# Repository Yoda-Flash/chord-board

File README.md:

# Chord Board
The Chord Board is a MIDI controller, specifically designed for one to experiment with chords! 
Each note you play can be customized and looped.

I came up with this idea because I've always loved playing with different chords. 
I thought it would be cool to be able to experiment with them without having an actual instrument with me, 
or needing to learn the chords and fingerings to hear different combinations.

## Images
### CAD
Top view:

Bottom view:

CAD of PCB with parts:

### PCB
PCB:

3D PCB Front:

3D PCB Back:

## Features
### Keypad
- 9 keys in a matrix
- 7 keys to activate chords
  - E.g. Pressing "I" will play the root chord, and "V" will play the fifth
- 2 keys to raise or lower the current key (default is C4)

### Rotary Potentiometers
- 7 knobs to modify chords
  - One knob for each note in the chord (1, 3, 5, 7, 9, 11, 13)
  - Each knob has 5 markings: ♭♭, ♭, no modification, #, ## (from left to right)
  - Modifications get applied to the next chord activated
  - If you don't want to include the note in the chord, just rotate the knob to any other position
  - E.g. If the 1st knob is not modified, the 2nd knob is at ♭, and the 3rd knob is not modified, a minor triad will play
- 1 logarithmic knob to adjust volume

### Slide potentiometer
- Inverts the chord depending on how much you slide
  - E.g. If a minor triad is playing and you slide 1/3 of the way, the base note will become the 5th

### Latching buttons
- 1 to cycle through different octaves, between octaves 2 to 6
- 1 to record a loop
  - When pressed, the chord sequence and timing will be recorded
  - When released, the chord sequence will be played back until you re-record or press another key

### TFT Display
- Displays the current key, including the octave, and the notes of the chord being played
  - If the notes being played are matched with a chord, that chord's name will be displayed as well

### Speakers
- Stereo sound
- Left and right speakers connected to a Class D Amplifier

### Power system
- 18650 3.7 V battery 
  - When a USB is plugged into the microcontroller, it will automatically charge
- Switch to power the board on/off
- A cover secures the battery, to be screwed open
  - Comes with a groove for fingers to easily remove the cover

### Stackable Case Cover
- The case comes with a cover, so the device can be transported without fear of accidentally pressing keys or rotating knobs
- The cover can be stacked on the bottom cover, so it doesn't have to lie around when the device is in use

## Bill of Materials
[CSV](bom.csv)

[Excel XLSX](bom.xlsx)

## How to Set Up

### Build Instructions
Gather the assembled PCB and the 3D printed pieces in the [cad folder](./cad), as well as 4 sets of M3 12mm screws and heat inserts and 1 set of M2 3mm screws and heat inserts. 

Use a soldering iron to set the heat inserts in their respective holes (M2 3mm into the bottom case's back holes for the battery cover and M3 12mm for the bottom case's top holes for PCB mounting). Then, place the PCB in between the top and bottom case, and a battery and its cover into the slot on the back. Use a 2mm hex key to screw in the M2 screws and a 3mm hex key for the M3 one.

### Firmware Instructions
The firmware uses Circuit Python, 
so get started with it following https://learn.adafruit.com/welcome-to-circuitpython/installing-circuitpython

Within the Circuit Python drive, 
use pip to install the requirements in `requirements.txt` and transfer the files from `./firmware` to use!

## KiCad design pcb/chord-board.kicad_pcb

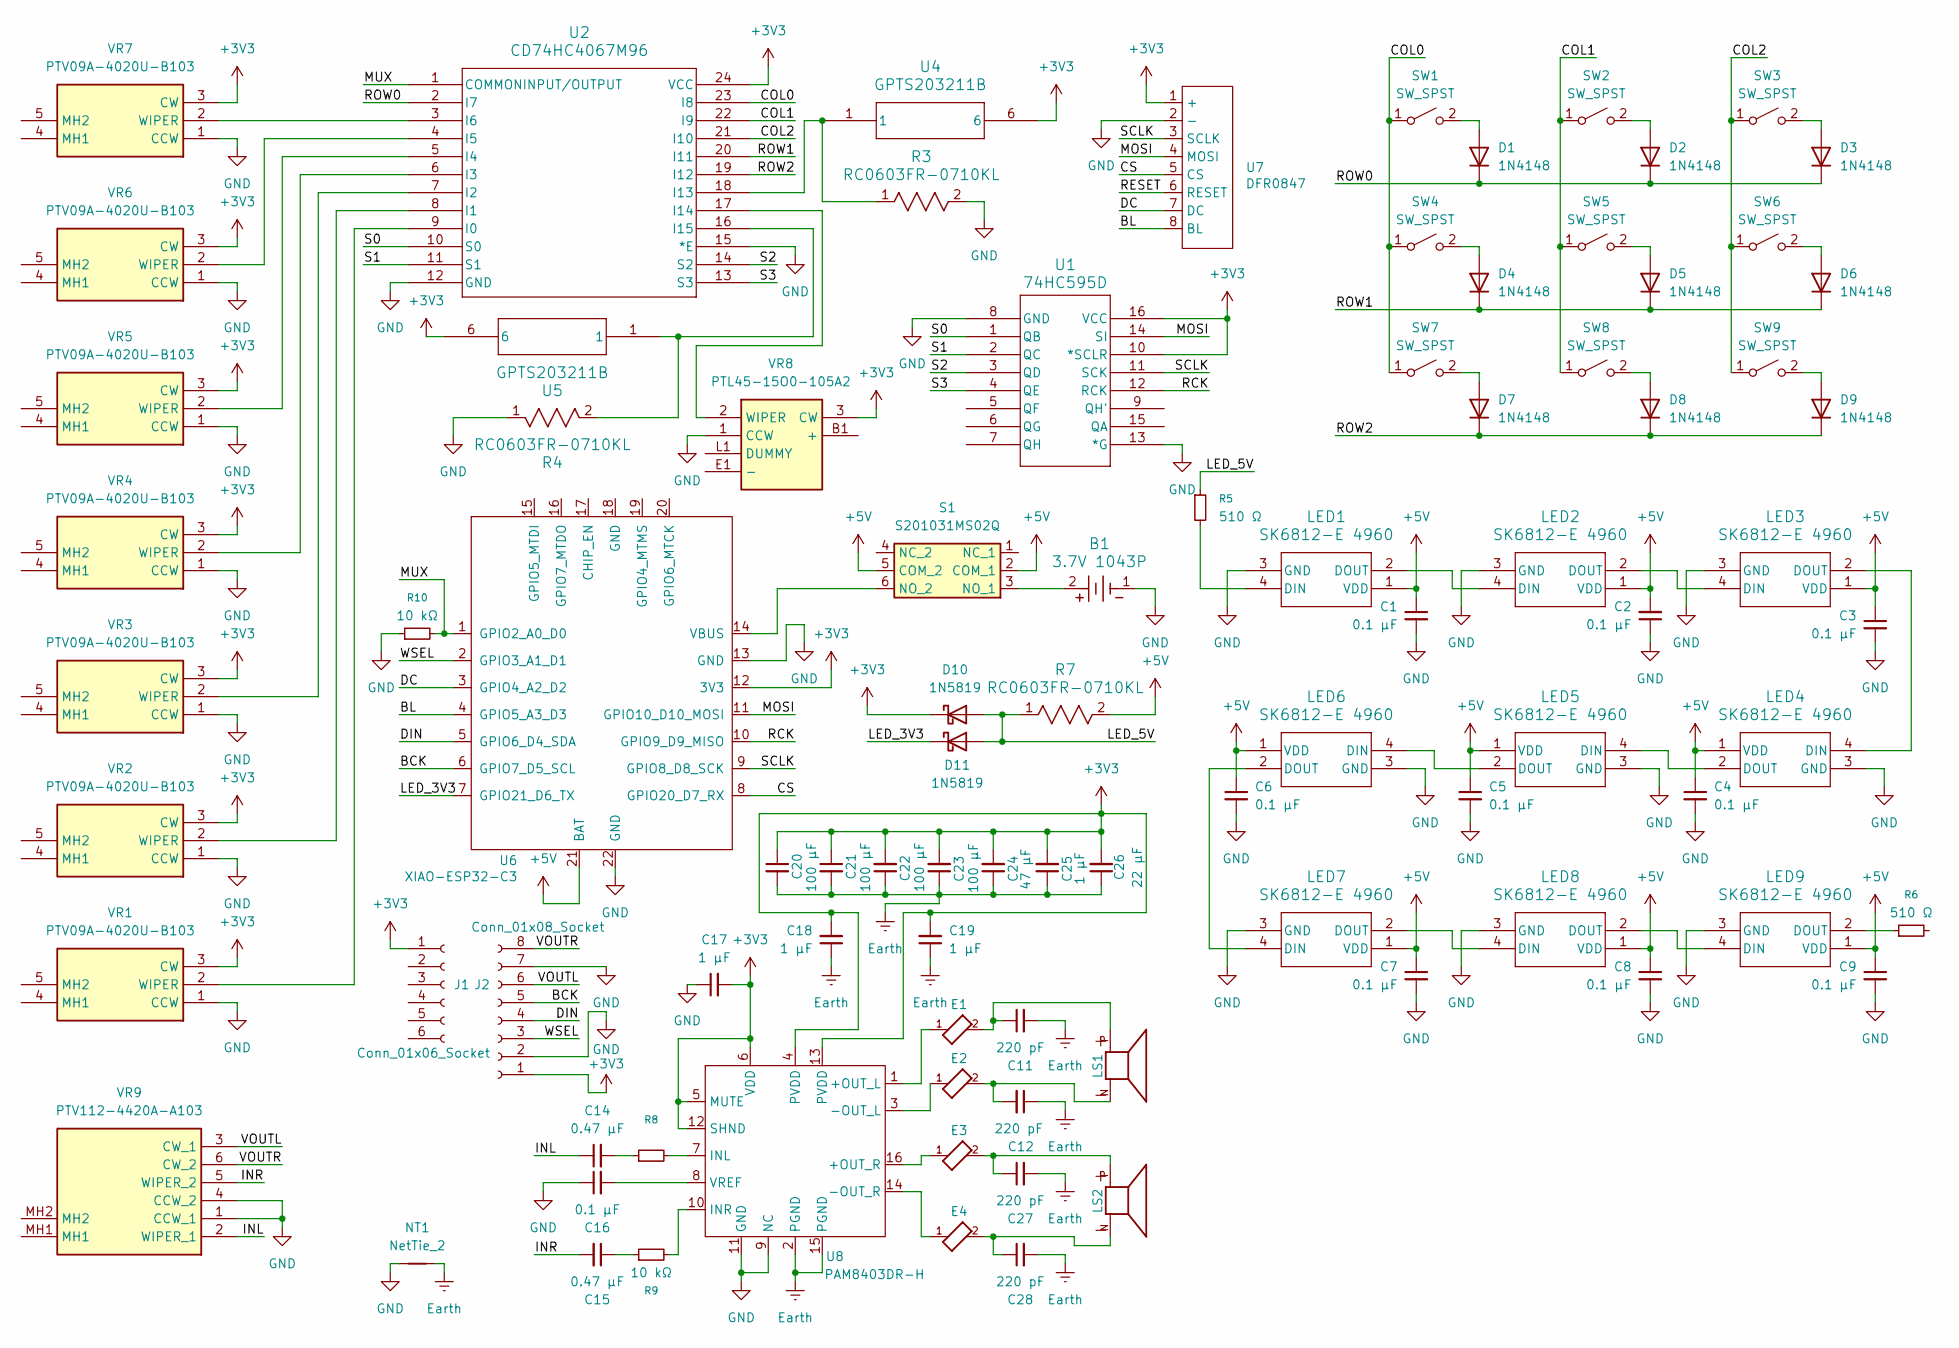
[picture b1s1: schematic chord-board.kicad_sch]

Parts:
B1: 3.7V 1043P; BATT_1043P_KEY
C1, C2, C3, C4, C5, C6, C7, C8, C9, C16: 0.1 µF; C_0603_1608Metric
C11, C12, C27, C28: 220 pF; C_0603_1608Metric
C14, C15: 0.47 µF; C_0603_1608Metric
C17, C18, C19, C25: 1 µF; C_0603_1608Metric
C20, C21, C22, C23: 100 µF; C_0805_2012Metric
C24: 47 µF; C_0805_2012Metric
C26: 22 µF; C_0603_1608Metric
D1, D2, D3, D4, D5, D6, D7, D8, D9: 1N4148; D_SOD-123
D10, D11: 1N5819; D_SOD-123F
E1, E2, E3, E4: MI0603L301R-10; FB_MI0603L301R-10
J1: Conn_01x06_Socket; PinSocket_1x06_P2.54mm_Vertical
J2: Conn_01x08_Socket; PinSocket_1x08_P2.54mm_Vertical
LED1, LED2, LED3, LED4, LED5, LED6, LED7, LED8, LED9: SK6812-E 4960; SK6812-E 4960_ADA
LS1, LS2: SMS-1804MS-HT; SPKR_SMS-1804MS-HT; PARTREV A
NT1: NetTie_2; NetTie-2_SMD_Pad0.5mm
R3, R4, R7: RC0603FR-0710KL; RC0603N_YAG
R5, R6: 510 Ω; BO_CR0603 510 Ohms
R8, R9: 10 kΩ; BO_CR0603 510 Ohms
R10: 10 kΩ; RC0603N_YAG
S1: S201031MS02Q; Manufacturer_Part_Number S201031MS02Q; Mouser Part Number 611-S201031MS02Q
SW1, SW2, SW3, SW4, SW5, SW6, SW7, SW8, SW9: SW_SPST; SW_Cherry_MX_1.00u_PCB
U1: 74HC595D; SOIC16_TOS
U2: CD74HC4067M96; CD74HC4067M96 DW24
U4, U5: GPTS203211B; SWITCH_03211B
U6: XIAO-ESP32-C3; XIAO-ESP32-C3-SMD
U7: DFR0847; DFR0874 SMD
U8: PAM8403DR-H
VR1, VR2, VR3, VR4, VR5, VR6, VR7: PTV09A-4020U-B103; PTV09A4020UB103; Manufacturer_Part_Number PTV09A-4020U-B103; Mouser Part Number 652-PTV09A-4020UB103
VR8: PTL45-15O0-105A2; PTL4515O0105A2; Manufacturer_Part_Number PTL45-15O0-105A2; Mouser Part Number 652-PTL45-15O0-105A2
VR9: PTV112-4420A-A103; PTV1124420AA103; Manufacturer_Part_Number PTV112-4420A-A103; Mouser Part Number 652-PTV112-4420AA103

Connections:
+3V3: C17.2, C18.2, C19.2, C20.1, C21.1, C22.2, C23.2, C24.2, C25.2, C26.2, D10.1 (K), J1.1 (Pin_1_1), J2.1, U1.10 (*SCLR), U1.16 (VCC), U2.24 (VCC), U4.6, U5.6, U6.12 (3V3), U7.1 (+), U8.4 (PVDD), U8.5 (MUTE), U8.6 (VDD), U8.12 (SHND), U8.13 (PVDD), VR1.3 (CW), VR2.3 (CW), VR3.3 (CW), VR4.3 (CW), VR5.3 (CW), VR6.3 (CW), VR7.3 (CW), VR8.3 (CW)
+5V: C1.1, C2.2, C3.1, C4.1, C5.1, C6.1, C7.1, C8.1, C9.1, LED1.1 (VDD), LED2.1 (VDD), LED3.1 (VDD), LED4.1 (VDD), LED5.1 (VDD), LED6.1 (VDD), LED7.1 (VDD), LED8.1 (VDD), LED9.1 (VDD), R7.2, S1.2 (COM_1), S1.5 (COM_2), U6.21 (BAT)
/BCK: J2.5, U6.6 (GPIO7_D5_SCL)
/BL: U6.4 (GPIO5_A3_D3), U7.8 (BL)
/COL0: SW1.1 (A), SW4.1 (A), SW7.1 (A), U2.23 (I8)
/COL1: SW2.1 (A), SW5.1 (A), SW8.1 (A), U2.22 (I9)
/COL2: SW3.1 (A), SW6.1 (A), SW9.1 (A), U2.21 (I10)
/CS: U6.8 (GPIO20_D7_RX), U7.5 (CS)
/DC: U6.3 (GPIO4_A2_D2), U7.7 (DC)
/DIN: J2.4, U6.5 (GPIO6_D4_SDA)
/INL: C14.1, VR9.2 (WIPER_1)
/INR: C15.2, VR9.5 (WIPER_2)
/LED_3V3: D11.1 (K), U6.7 (GPIO21_D6_TX)
/LED_5V: D10.2 (A), D11.2 (A), R5.1, R7.1
/MOSI: U1.14 (SI), U6.11 (GPIO10_D10_MOSI), U7.4 (MOSI)
/MUX: R10.2, U2.1 (COMMONINPUT/OUTPUT), U6.1 (GPIO2_A0_D0)
/RCK: U1.12 (RCK), U6.10 (GPIO9_D9_MISO)
/RESET: U7.6 (RESET)
/ROW0: D1.1 (K), D2.1 (K), D3.1 (K), U2.2 (I7)
/ROW1: D4.1 (K), D5.1 (K), D6.1 (K), U2.20 (I11)
/ROW2: D7.1 (K), D8.1 (K), D9.1 (K), U2.19 (I12)
/S0: U1.1 (QB), U2.10 (S0)
/S1: U1.2 (QC), U2.11 (S1)
/S2: U1.3 (QD), U2.14 (S2)
/S3: U1.4 (QE), U2.13 (S3)
/SCLK: U1.11 (SCK), U6.9 (GPIO8_D8_SCK), U7.3 (SCLK)
/VOUTL: J2.6, VR9.3 (CW_1)
/VOUTR: J2.8, VR9.6 (CW_2)
/WSEL: J2.3, U6.2 (GPIO3_A1_D1)
Earth: C11.2, C12.1, C18.1, C19.1, C20.2, C21.2, C22.1, C23.1, C24.1, C25.1, C26.1, C27.2, C28.2, NT1.2, U8.2 (PGND), U8.15 (PGND)
GND: B1.1, C1.2, C2.1, C3.2, C4.2, C5.2, C6.2, C7.2, C8.2, C9.2, C16.1, C17.1, J2.2, J2.7, LED1.3 (GND), LED2.3 (GND), LED3.3 (GND), LED4.3 (GND), LED5.3 (GND), LED6.3 (GND), LED7.3 (GND), LED8.3 (GND), LED9.3 (GND), NT1.1, R3.2, R4.1, R10.1, U1.8 (GND), U1.13 (*G), U2.12 (GND), U2.15 (*E), U6.13 (GND), U6.22 (GND), U7.2 (-), U8.9 (NC), U8.11 (GND), VR1.1 (CCW), VR2.1 (CCW), VR3.1 (CCW), VR4.1 (CCW), VR5.1 (CCW), VR6.1 (CCW), VR7.1 (CCW), VR8.1 (CCW), VR9.1 (CCW_1), VR9.4 (CCW_2)
unnamed: C11.1, E1.2, LS1.P
unnamed: C12.2, E2.2, LS1.N
unnamed: C14.2, R8.1
unnamed: C15.1, R9.1
unnamed: C27.1, E3.2, LS2.P
unnamed: C28.1, E4.2, LS2.N
unnamed: D1.2 (A), SW1.2 (B)
unnamed: D2.2 (A), SW2.2 (B)
unnamed: D3.2 (A), SW3.2 (B)
unnamed: D4.2 (A), SW4.2 (B)
unnamed: D5.2 (A), SW5.2 (B)
unnamed: D6.2 (A), SW6.2 (B)
unnamed: D7.2 (A), SW7.2 (B)
unnamed: D8.2 (A), SW8.2 (B)
unnamed: D9.2 (A), SW9.2 (B)
unnamed: LED1.4 (DIN), R5.2
unnamed: LED1.2 (DOUT), LED2.4 (DIN)
unnamed: LED2.2 (DOUT), LED3.4 (DIN)
unnamed: LED3.2 (DOUT), LED4.4 (DIN)
unnamed: LED4.2 (DOUT), LED5.4 (DIN)
unnamed: LED5.2 (DOUT), LED6.4 (DIN)
unnamed: LED6.2 (DOUT), LED7.4 (DIN)
unnamed: LED7.2 (DOUT), LED8.4 (DIN)
unnamed: LED8.2 (DOUT), LED9.4 (DIN)
unnamed: LED9.2 (DOUT), R6.1
unnamed: B1.2, S1.3 (NO_1)
unnamed: S1.6 (NO_2), U6.14 (VBUS)
unnamed: U2.9 (I0), VR1.2 (WIPER)
unnamed: U2.8 (I1), VR2.2 (WIPER)
unnamed: U2.7 (I2), VR3.2 (WIPER)
unnamed: U2.6 (I3), VR4.2 (WIPER)
unnamed: U2.5 (I4), VR5.2 (WIPER)
unnamed: U2.4 (I5), VR6.2 (WIPER)
unnamed: U2.3 (I6), VR7.2 (WIPER)
unnamed: R3.1, U2.18 (I13), U4.1
unnamed: U2.17 (I14), VR8.2 (WIPER)
unnamed: R4.2, U2.16 (I15), U5.1
unnamed: E1.1, U8.1 (+OUT_L)
unnamed: E3.1, U8.16 (+OUT_R)
unnamed: E2.1, U8.3 (-OUT_L)
unnamed: E4.1, U8.14 (-OUT_R)
unnamed: R8.2, U8.7 (INL)
unnamed: R9.2, U8.10 (INR)
unnamed: C16.2, U8.8 (VREF)

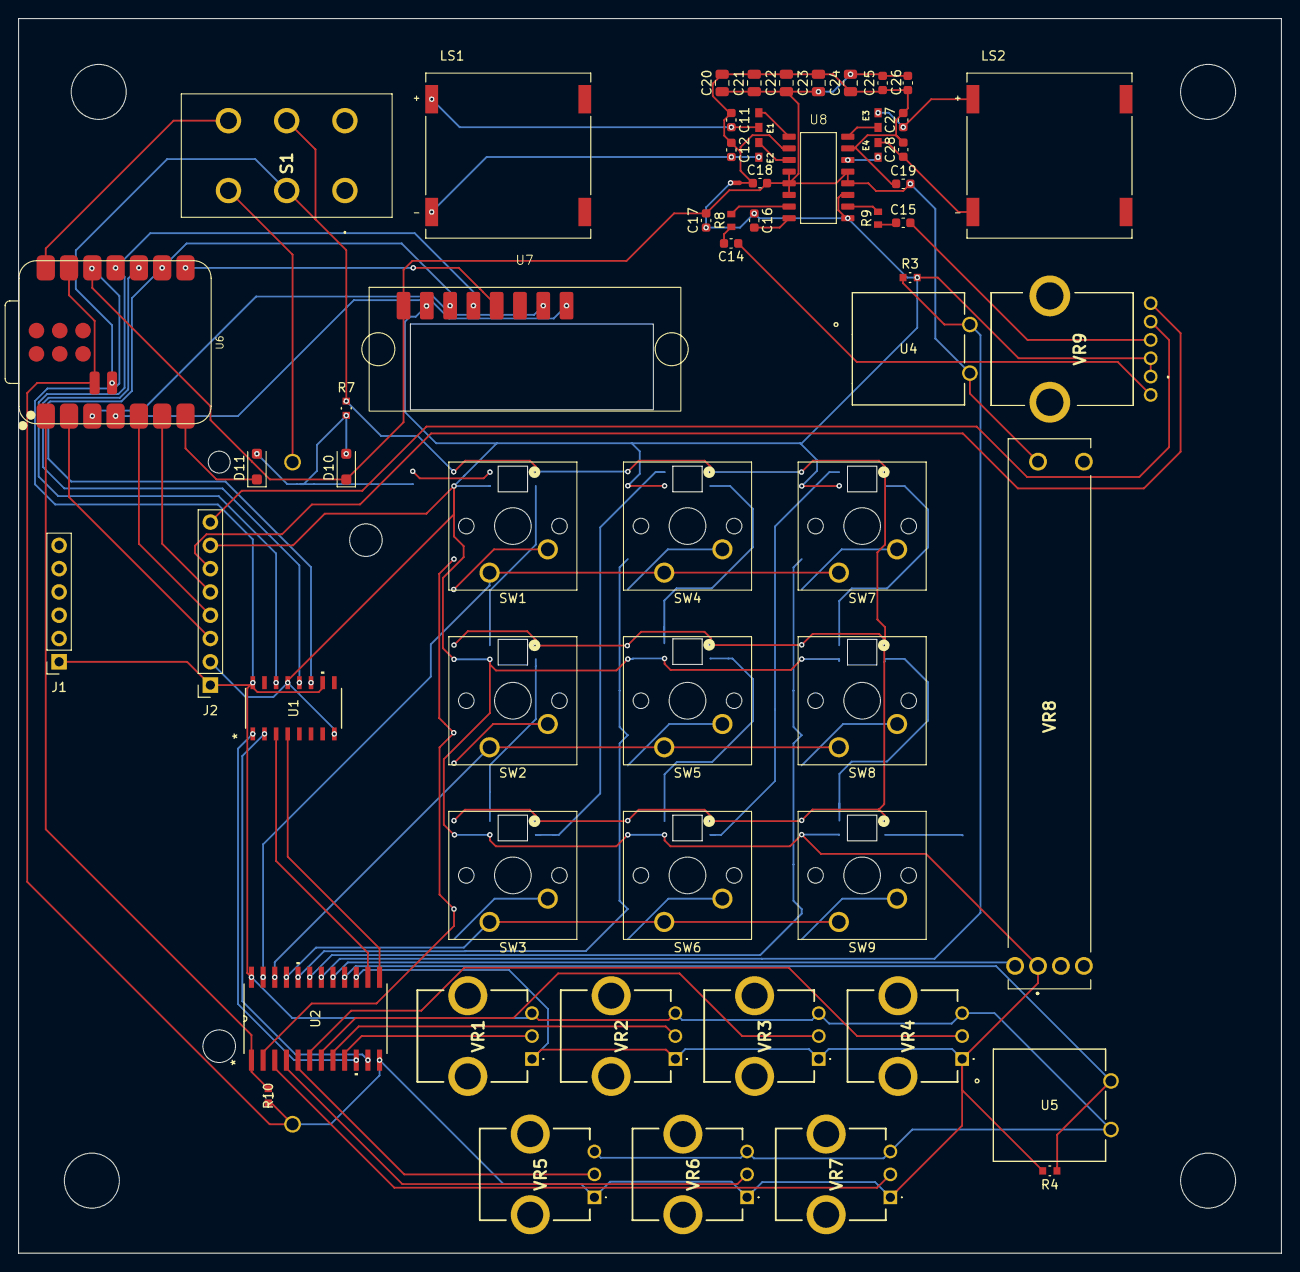
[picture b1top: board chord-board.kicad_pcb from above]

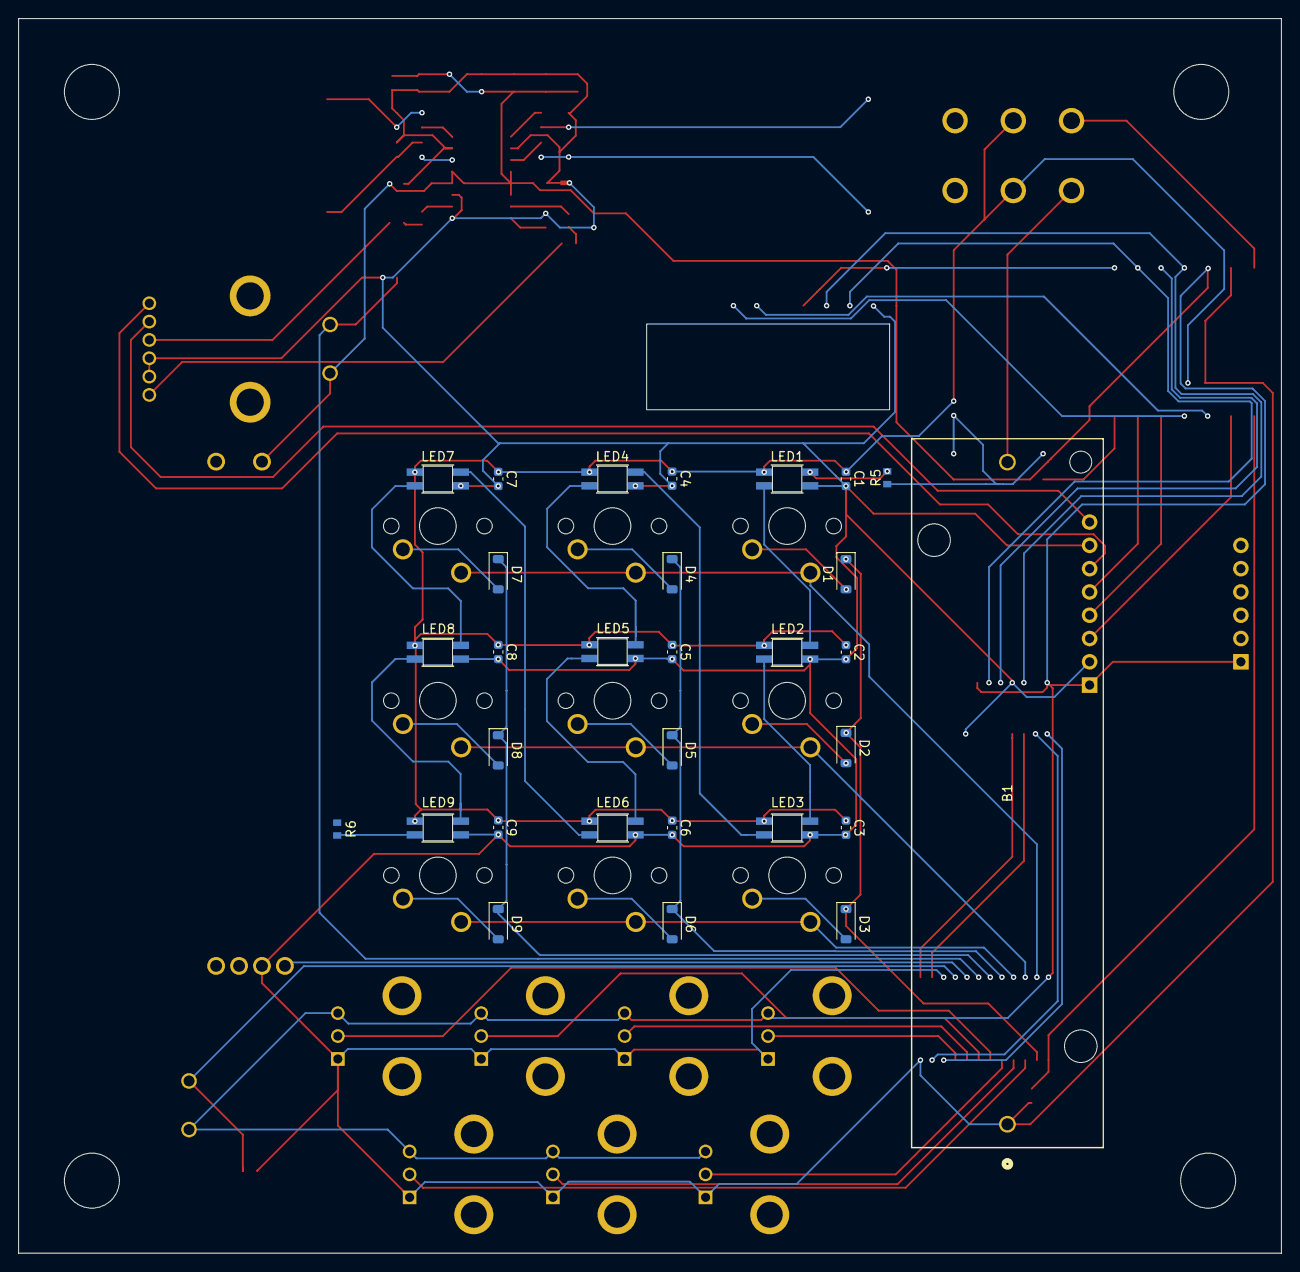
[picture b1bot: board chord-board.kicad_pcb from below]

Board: 2 copper layers, 137.7 x 134.7 mm, 90 parts (30 on the bottom side), 74 nets.

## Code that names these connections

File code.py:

import math

import board
import terminalio
from displayio import Group, release_displays
from adafruit_display_text import label
from adafruit_74hc595 import ShiftRegister74HC595
from adafruit_st7735 import ST7735
from analogio import AnalogIn, AnalogOut
from audiobusio import I2SOut
from digitalio import DigitalInOut, Direction
from fourwire import FourWire
from synthio import Synthesizer

from midi_tools import note_or_name

board_voltage = 3.3
voltage_tolerance = 0.5

# Shift register init
sr_latch_pin = DigitalInOut(board.D9)
sr = ShiftRegister74HC595(board.SPI(), sr_latch_pin)

select_pins = [sr.get_pin(pin) for pin in range(1, 5)]
for pin in select_pins:
    pin.direction = Direction.OUTPUT

# Analog multiplexer init

mux_pin = AnalogIn(board.A0)
# mux_pins = ["1", "3", "5", "7", "9", "11", "13", "row0", "col0", "col1", "col2", "row1", "row2", "loop", "invert", "octave"]

# Inputs init
row_pins = [7, 11, 12]
col_pins = [8, 9, 10]
keys = [["I", "II", "III"], ["IV", "V", "VI"], ["VII", "keyup", "keydown"]]
chord_labels = ["I", "II", "III", "IV", "V", "VI", "VII"]
pressed_keys = []

pot_voltage_bounds = [[0.0, 0.5], [0.6, 1.0], [1.2, 1.8], [2.0, 2.6], [2.8, 3.3]] # TODO: Fill with actual voltage max/min boundary at each marking when testing the physical board

invert_pin = 14
octave_pin = 13
loop_pin = 15

# TFT screen init
release_displays()

display_bus = FourWire(board.SPI(), command=board.D2, chip_select=board.D7)
display = ST7735(display_bus, width=160, height=80, rotation=180)

splash = Group()
text_group = Group(scale=2, x=10, y=10) # TODO: Figure out a good offset for the words when testing physical board

# DAC for speaker init
audio = I2SOut(board.D5, board.D1, board.D4)

# Synth for playing music
synth = Synthesizer(sample_rate=44100)
audio.play(synth)

# Processing variables init
current_octave = 4
current_key = note_or_name(f"C{current_octave}")
root_note = current_key
rel_notes = []
notes = []

CHORD_NAMES = {
    "maj": [0, 4, 7],
    "min": [0, 3, 7],
    "aug": [0, 4, 8],
    "dim": [0, 3, 6],
    "sus": [0, 5, 7],
    "sus2": [0, 2, 7],
    "6": [0, 4, 7, 9],
    "(add2), (add9)": [0, 2, 4, 7],
    "maj7": [0, 4, 7, 11],
    "7": [0, 4, 7, 10],
    "7♭5": [0, 4, 6, 10],
    "7sus": [0, 5, 7, 10],
    "m(add2), m(add9)": [0, 2, 3, 7],
    "m6": [0, 3, 7, 9],
    "m7": [0, 3, 7, 10],
    "m(maj7)": [0, 3, 7, 11],
    "m7♭5": [0, 3, 6, 10],
    "dim7": [0, 3, 6, 9],
    "5": [0, 7],
    "maj7♯11": [0, 4, 7, 11, 18],
    "maj9": [0, 4, 7, 11, 14],
    "7♯9": [0, 4, 7, 10, 15],
    "9": [0, 4, 7, 10, 14],
    "11, 9(sus4)": [0, 7, 10, 14, 17],
    "13": [0, 4, 7, 10, 14, 21],
    "m9": [0, 3, 7, 10, 14],
    "m11": [0, 3, 7, 10, 17]
}

chord_sequence = []
timer = 0
time_sequence = []
is_recording_loop = False
loop_pos = 0

def get_analog_voltage(mux_pin):
    return (mux_pin.value / 65536)*board_voltage


def number_to_bits(number):
    number = number & 0xF
    return format(number, '04b')


def bits_to_booleans(bits: str):
    booleans = []
    for bit in bits:
        booleans.append(True if bit == '1' else False)
    return booleans


def set_select_pins(pin, select_pins):
    booleans = bits_to_booleans(number_to_bits(pin))
    i = 0
    while i < 4:
        select_pins[i].value = booleans[i]
        i += 1


def raise_key(key):
    key += 1
    if key > note_or_name(f"C{current_octave+1}"):
        key - 12
    return key


def lower_key(key):
    key -= 1
    if key < note_or_name(f"C{current_octave-1}"):
        key + 12
    return key


def get_rel_note_num_from_index(index):
    return index*2


def get_note_mod_from_index(index):
    return index - 2


def invert_chord(notes, voltage):
    num_inversions = math.floor(board_voltage - voltage)/(board_voltage/len(notes)) # Assuming linear voltage by slider's distance, divide voltage by the proportion of the slider's distance
    if num_inversions == 0:
        return notes
    shifted_notes = [(note - 12) for note in notes[-num_inversions:]]
    del notes[-num_inversions:]
    return shifted_notes + notes


def cycle_octave(octave):
    octave += 1
    if octave > 6:
        octave = 2
    return octave


def update_key(key):
    keystring = note_or_name(key)[:1] # Isolates the key without the octave designation
    return note_or_name(f"{keystring}{current_octave}")


def next_loop_pos(pos, len):
    pos += 1
    if pos >= len:
        pos = 0
    return pos


def get_chord_notes(notes):
    return "  ".join(notes)


def get_chord_name(rel_notes):
    reordered_notes = [note + 12 if note < 0 else note for note in rel_notes]

    for name, notes in CHORD_NAMES.items():
        if notes == reordered_notes:
            return f" - {name}"
    return ""


def get_base_note(notes):
    if notes[0] != 0:
        return f" / {note_or_name(notes[0])}"
    else:
        return ""

while True:
    # Read from Analog Multiplexer first
    pin_readings = []
    pressed_keys = []
    for pin in range(0, 16):
        set_select_pins(pin, select_pins)

        pin_readings.append(get_analog_voltage(mux_pin))

        if pin in row_pins:
            mux_pin.deinit()
            mux_pin = AnalogOut(board.A0)
            mux_pin.value = 0
            for col in col_pins:
                set_select_pins(col, select_pins)

                mux_pin.deinit()
                mux_pin = AnalogIn(board.A0)
                if abs(get_analog_voltage(mux_pin)-board_voltage) <= voltage_tolerance:
                    pressed_keys.append(keys[pin][col])

    pot_readings = pin_readings[:7]
    for reading_index, reading in enumerate(pot_readings):
        for bound_index, bound in enumerate(pot_voltage_bounds):
            if bound[0] <= reading <= bound[1]:
                note = get_rel_note_num_from_index(reading_index)
                mod = get_note_mod_from_index(bound_index)
                rel_notes.append(note + mod)
                break

    invert_chord(rel_notes, pin_readings[invert_pin])

    if abs(pin_readings[octave_pin] - board_voltage) < voltage_tolerance:
        current_octave = cycle_octave(current_octave)
        current_key = update_key(current_key)

    if abs(pin_readings[loop_pin] - board_voltage) < voltage_tolerance:
        if not is_recording_loop: #Reset at the beginning of each record
            chord_sequence.clear()
            time_sequence.clear()
            timer = 0
            loop_pos = 0
            is_recording_loop = True
        timer += 1
    else:
        if is_recording_loop:
            time_sequence.append(timer)
            timer = 0
            is_recording_loop = False
        if timer > time_sequence[loop_pos]:
            synth.release(chord_sequence[loop_pos])
            loop_pos = next_loop_pos(loop_pos, len(time_sequence))
            synth.press(chord_sequence[loop_pos])

        timer += 1

    for key in pressed_keys:
        if key in chord_labels:
            root_note = current_key + chord_labels.index(key)
            synth.release(notes)
            notes.clear()

            notes = [int(note + root_note) for note in rel_notes]
            synth.press(notes)

            text = f"{note_or_name(current_key)}{get_chord_name(rel_notes)}{get_base_note(notes)} \n {get_chord_notes(notes)}"
            text_label = label.Label(terminalio.FONT, text=text)
            text_group.append(text_label)
            splash.append(text_group)

            if is_recording_loop:
                if timer != 0:
                    time_sequence.append(timer)
                    timer = 0
                chord_sequence.append(notes)

        elif key == "keyup":
            current_key = raise_key(current_key)
        elif key == "keydown":
            current_key = lower_key(current_key)

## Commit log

2026-06-18 Rough version of analog multiplexer and keyboard code done
2026-06-19 Finished all input code
2026-06-19 I should've added the TFT screen code!
2026-06-19 Finished the BOM and the README!
2026-06-20 Added Zine page to everything
2026-06-20 Tracked CAD files with LFS
2026-06-20 Cleaned up everything; should be ready to submit!
2026-06-20 Added firmware instructions to README
2026-06-20 Added firmware instructions to README, PCB price to BOM, and removed boundaries from Zine
2026-06-20 Moved assembly CAD to production folder
2026-06-21 Update README.md with build instructions
